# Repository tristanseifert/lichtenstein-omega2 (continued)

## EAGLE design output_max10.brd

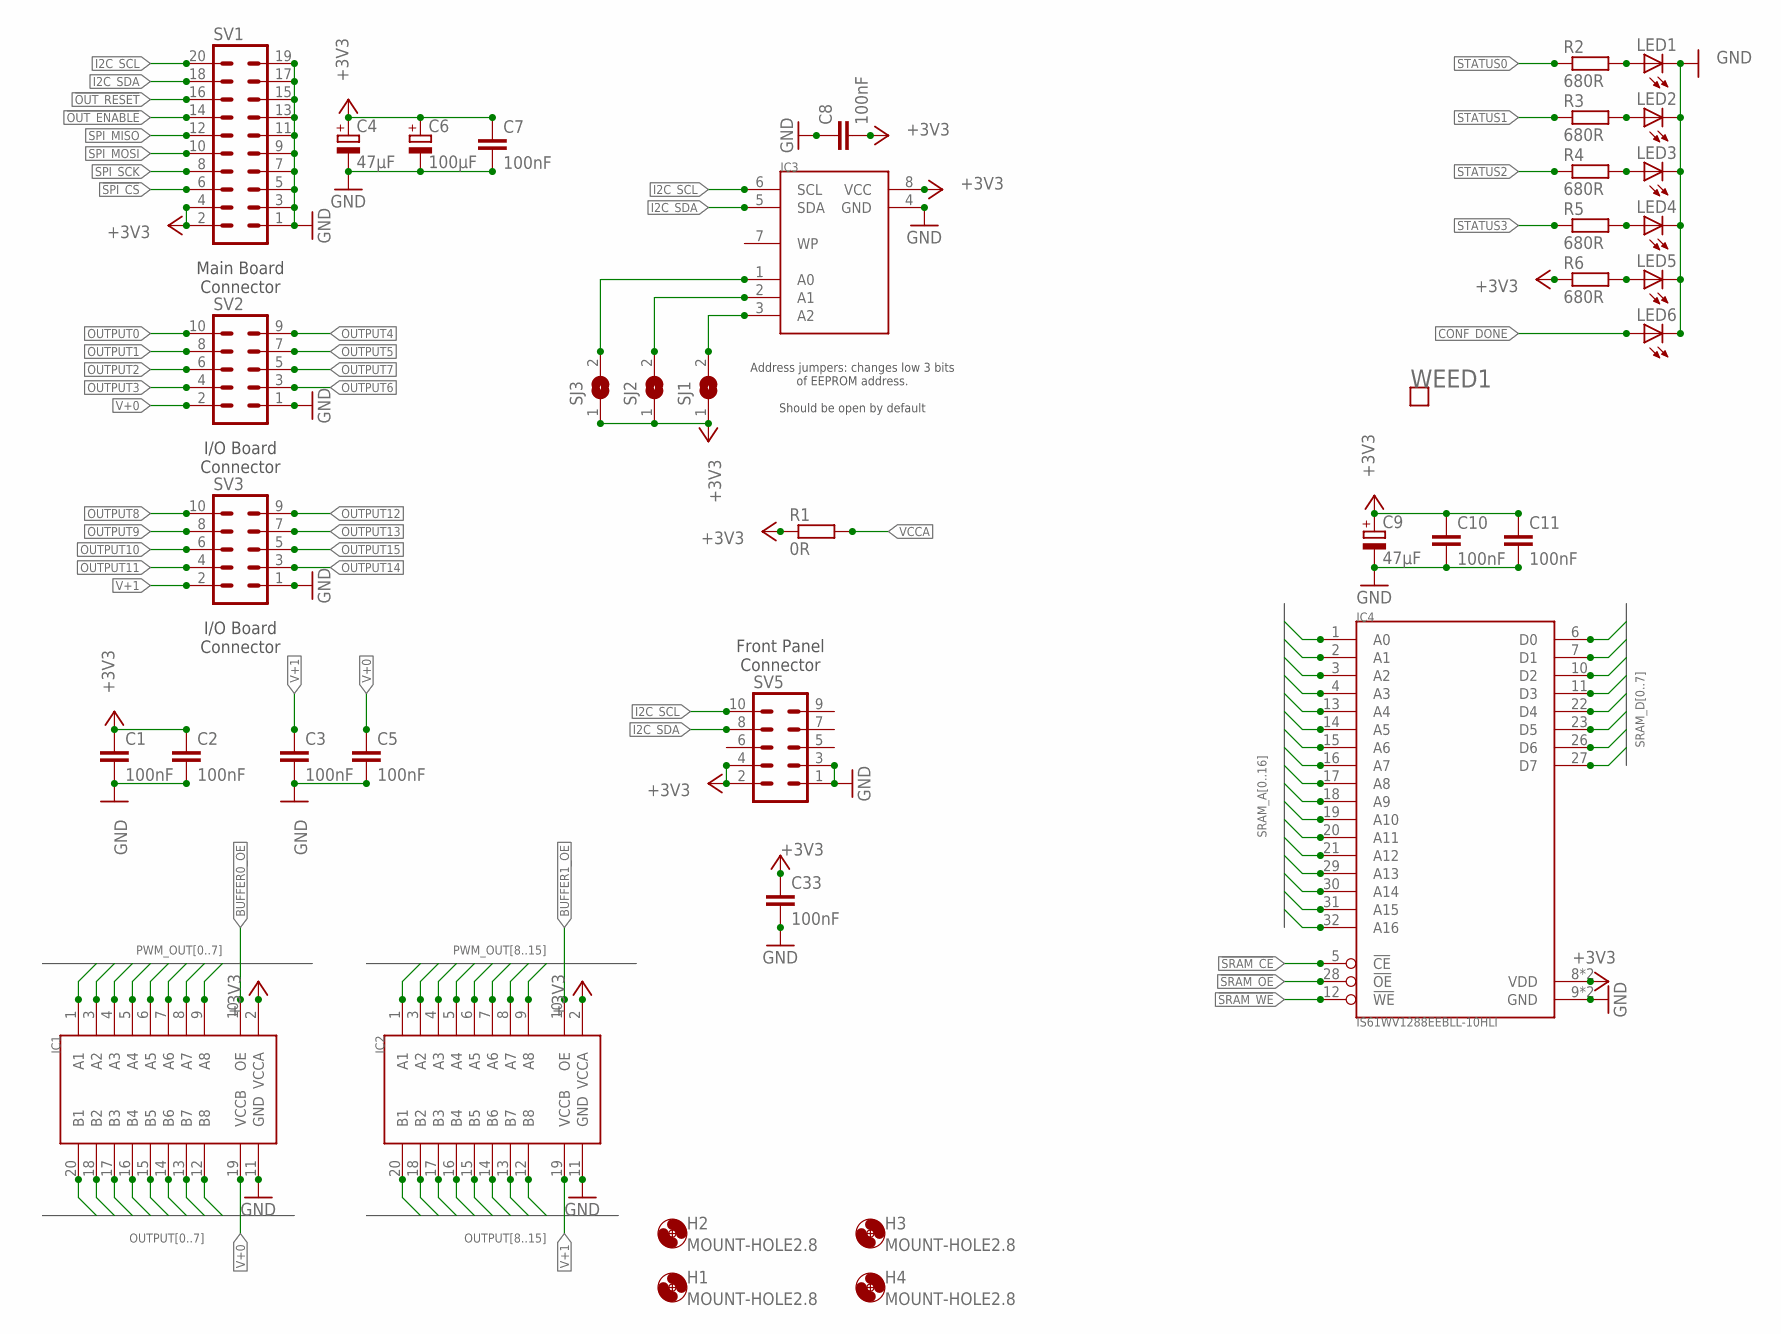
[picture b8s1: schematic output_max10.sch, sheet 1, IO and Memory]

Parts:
C1, C2, C3, C5, C7, C8, C10, C11, C33: 100nF; C0805; MOUSER 710-885012207072
C4, C9: 47µF; CT7343; MOUSER 581-TAJD476M016RNJV
C6: 100µF; CT7343; MOUSER 581-NOSD107M006
H1, H2, H3, H4: MOUNT-HOLE2.8; 2,8
IC1, IC2: TXB0108TSSOP20; TSSOP20
IC3: AT24C02DSOIC-8; SOIC8
IC4: IS61WV1288EEBLL-10HLI; TSOP8X16; MOUSER 870-61WV1288ELL10HLI
LED1: LEDCHIPLED_1206; CHIPLED_1206; MOUSER 604-APTR3216SRCPRV
LED2, LED3, LED4, LED5, LED6: LEDCHIPLED_1206; CHIPLED_1206; MOUSER 604-APTR3216SGC
R1: 0R; R2012; MOUSER 623-2508056017Y2
R2, R3, R4, R5, R6: 680R; M0805; MOUSER 652-CR0805-FX6800GLF
SJ1, SJ2, SJ3: SJ
SV1: MA10-2; MOUSER 517-30320-6002
SV2, SV3, SV5: MA05-2; MOUSER 517-30310-6002
WEED1: WEED; DOINK

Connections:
!OUT_ENABLE: SV1.14; also elsewhere on the board
!OUT_RESET: SV1.16; also elsewhere on the board
!SPI_CS: SV1.6; also elsewhere on the board
!SRAM_CE: IC4.5 (!CE); also elsewhere on the board
!SRAM_OE: IC4.28 (!OE); also elsewhere on the board
!SRAM_WE: IC4.12 (!WE); also elsewhere on the board
+3V3: C1.1, C2.1, C4.+, C6.+, C7.1, C8.2, C9.+, C10.1, C11.1, C33.1, IC1.2 (VCCA), IC2.2 (VCCA), IC3.8 (VCC), IC4.8 (VDD), IC4.24 (VDD), R1.1, R6.1, SJ1.1, SJ2.1, SJ3.1, SV1.2, SV1.4, SV5.2, SV5.4; also elsewhere on the board
BUFFER0_OE: IC1.10 (OE); also elsewhere on the board
BUFFER1_OE: IC2.10 (OE); also elsewhere on the board
CONF_DONE: LED6.A; also elsewhere on the board
GND: C1.2, C2.2, C3.2, C4.-, C5.2, C6.-, C7.2, C8.1, C9.-, C10.2, C11.2, C33.2, IC1.11 (GND), IC2.11 (GND), IC3.4 (GND), IC4.9 (GND), IC4.25 (GND), LED1.C, LED2.C, LED3.C, LED4.C, LED5.C, LED6.C, SV1.1, SV1.3, SV1.5, SV1.7, SV1.9, SV1.11, SV1.13, SV1.15, SV1.17, SV1.19, SV2.1, SV3.1, SV5.1, SV5.3; also elsewhere on the board
I2C_SCL: IC3.6 (SCL), SV1.20, SV5.10
I2C_SDA: IC3.5 (SDA), SV1.18, SV5.8
unnamed: LED3.A, R4.2
unnamed: LED4.A, R5.2
unnamed: LED5.A, R6.2
unnamed: IC3.3 (A2), SJ1.2
unnamed: IC3.2 (A1), SJ2.2
unnamed: IC3.1 (A0), SJ3.2
unnamed: LED1.A, R2.2
unnamed: LED2.A, R3.2
OUTPUT0: IC1.20 (B1), SV2.10
OUTPUT1: IC1.18 (B2), SV2.8
OUTPUT2: IC1.17 (B3), SV2.6
OUTPUT3: IC1.16 (B4), SV2.4
OUTPUT4: IC1.15 (B5), SV2.9
OUTPUT5: IC1.14 (B6), SV2.7
OUTPUT6: IC1.13 (B7), SV2.3
OUTPUT7: IC1.12 (B8), SV2.5
OUTPUT8: IC2.20 (B1), SV3.10
OUTPUT9: IC2.18 (B2), SV3.8
OUTPUT10: IC2.17 (B3), SV3.6
OUTPUT11: IC2.16 (B4), SV3.4
OUTPUT12: IC2.15 (B5), SV3.9
OUTPUT13: IC2.14 (B6), SV3.7
OUTPUT14: IC2.13 (B7), SV3.3
OUTPUT15: IC2.12 (B8), SV3.5
PWM_OUT0: IC1.9 (A8); also elsewhere on the board
PWM_OUT1: IC1.8 (A7); also elsewhere on the board
PWM_OUT2: IC1.7 (A6); also elsewhere on the board
PWM_OUT3: IC1.6 (A5); also elsewhere on the board
PWM_OUT4: IC1.5 (A4); also elsewhere on the board
PWM_OUT5: IC1.4 (A3); also elsewhere on the board
PWM_OUT6: IC1.3 (A2); also elsewhere on the board
PWM_OUT7: IC1.1 (A1); also elsewhere on the board
PWM_OUT8: IC2.9 (A8); also elsewhere on the board
PWM_OUT9: IC2.8 (A7); also elsewhere on the board
PWM_OUT10: IC2.7 (A6); also elsewhere on the board
PWM_OUT11: IC2.6 (A5); also elsewhere on the board
PWM_OUT12: IC2.5 (A4); also elsewhere on the board
PWM_OUT13: IC2.4 (A3); also elsewhere on the board
PWM_OUT14: IC2.3 (A2); also elsewhere on the board
PWM_OUT15: IC2.1 (A1); also elsewhere on the board
SPI_MISO: SV1.12; also elsewhere on the board
SPI_MOSI: SV1.10; also elsewhere on the board
SPI_SCK: SV1.8; also elsewhere on the board
SRAM_A0: IC4.1 (A0); also elsewhere on the board
SRAM_A1: IC4.2 (A1); also elsewhere on the board
SRAM_A2: IC4.3 (A2); also elsewhere on the board
SRAM_A3: IC4.4 (A3); also elsewhere on the board
SRAM_A4: IC4.13 (A4); also elsewhere on the board
SRAM_A5: IC4.14 (A5); also elsewhere on the board
SRAM_A6: IC4.15 (A6); also elsewhere on the board
SRAM_A7: IC4.16 (A7); also elsewhere on the board
SRAM_A8: IC4.17 (A8); also elsewhere on the board
SRAM_A9: IC4.18 (A9); also elsewhere on the board
SRAM_A10: IC4.19 (A10); also elsewhere on the board
SRAM_A11: IC4.20 (A11); also elsewhere on the board
SRAM_A12: IC4.21 (A12); also elsewhere on the board
SRAM_A13: IC4.29 (A13); also elsewhere on the board
SRAM_A14: IC4.30 (A14); also elsewhere on the board
SRAM_A15: IC4.31 (A15); also elsewhere on the board
SRAM_A16: IC4.32 (A16); also elsewhere on the board
SRAM_D0: IC4.6 (D0); also elsewhere on the board
SRAM_D1: IC4.7 (D1); also elsewhere on the board
SRAM_D2: IC4.10 (D2); also elsewhere on the board
SRAM_D3: IC4.11 (D3); also elsewhere on the board
SRAM_D4: IC4.22 (D4); also elsewhere on the board
SRAM_D5: IC4.23 (D5); also elsewhere on the board
SRAM_D6: IC4.26 (D6); also elsewhere on the board
SRAM_D7: IC4.27 (D7); also elsewhere on the board
STATUS0: R2.1; also elsewhere on the board
STATUS1: R3.1; also elsewhere on the board
STATUS2: R4.1; also elsewhere on the board
STATUS3: R5.1; also elsewhere on the board
V+0: C5.1, IC1.19 (VCCB), SV2.2
V+1: C3.1, IC2.19 (VCCB), SV3.2
VCCA: R1.2; also elsewhere on the board

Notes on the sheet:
Main Board Connector
I/O Board Connector
Front Panel Connector
Address jumpers: changes low 3 bits of EEPROM address. Should be open by default

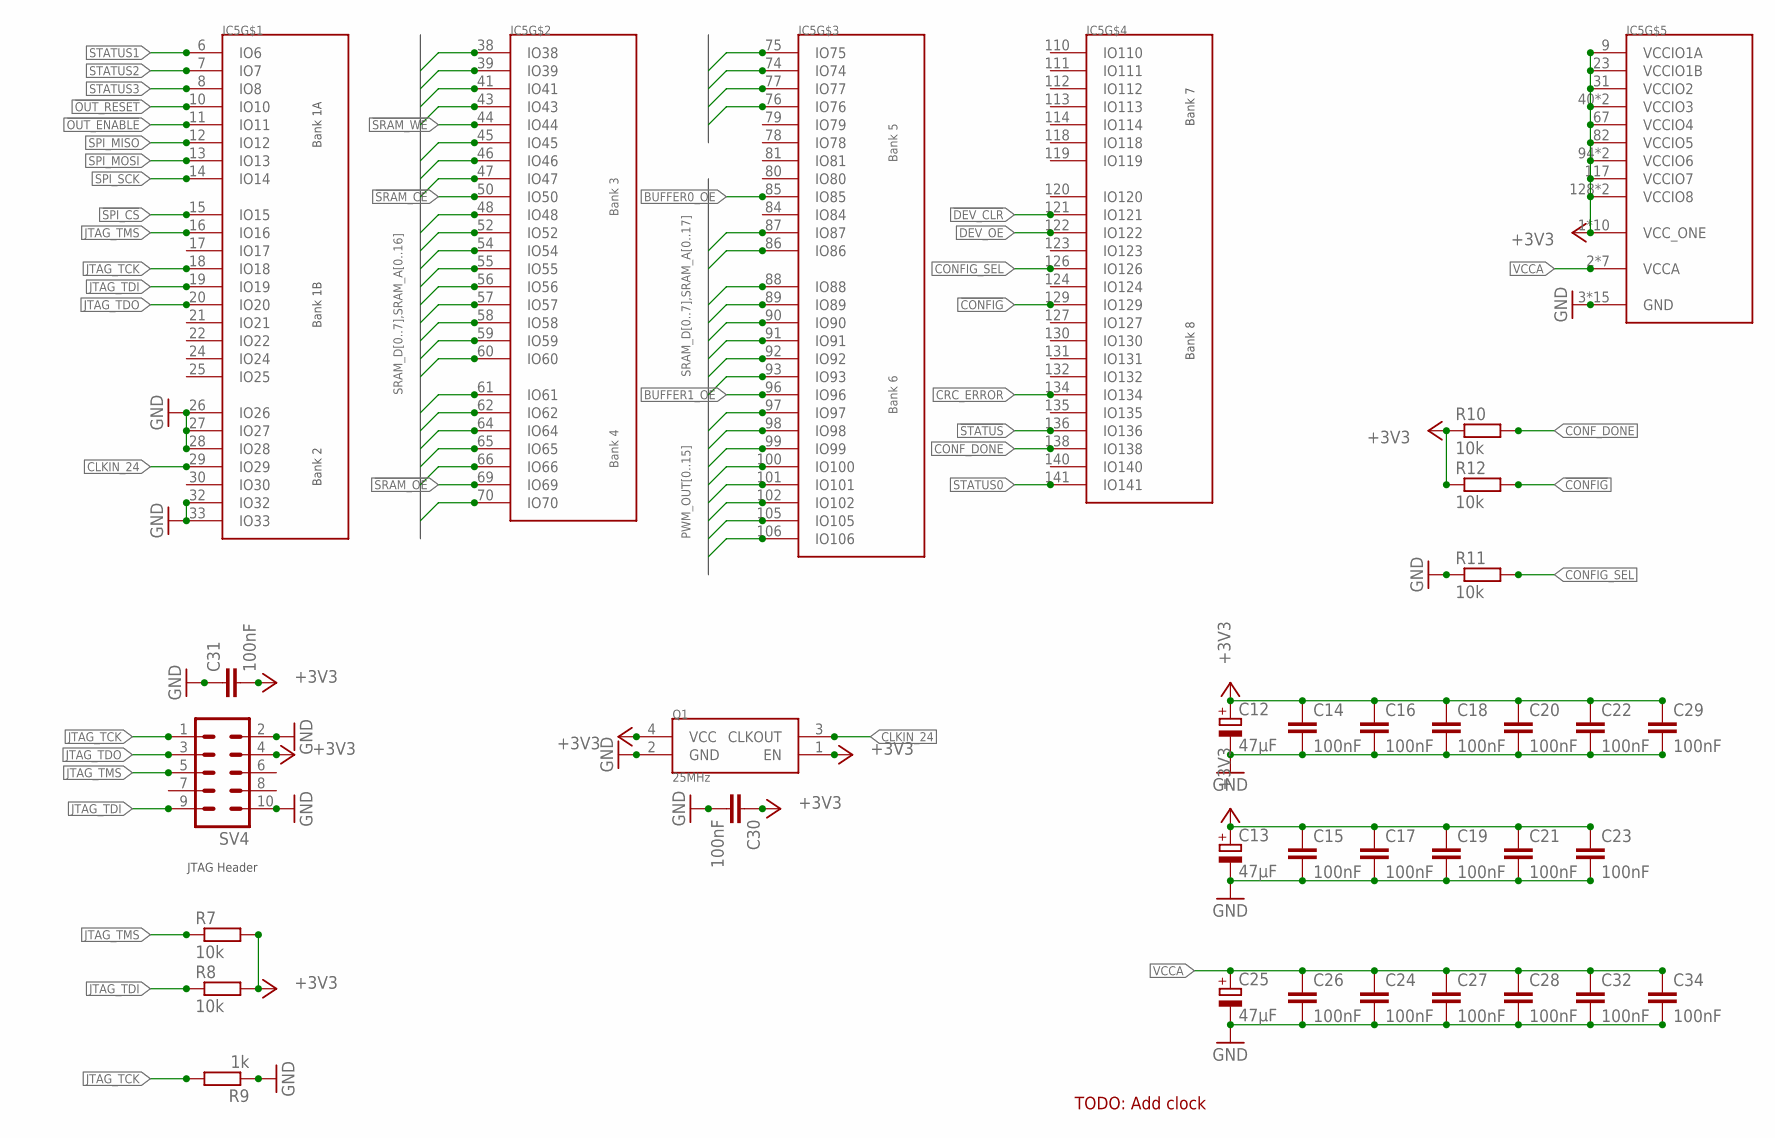
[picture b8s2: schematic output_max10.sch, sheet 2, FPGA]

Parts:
C12, C13, C25: 47µF; CT7343; MOUSER 581-TAJD476M016RNJV
C14, C15, C16, C17, C18, C19, C20, C21, C22, C23, C24, C26, C27, C28, C29, C30, C31, C32, C34: 100nF; C0805; MOUSER 710-885012207072
IC5: 10M04EQFP144; EQFP144; MOUSER 989-10M04SCE144C8G
Q1: 25MHz; VLGA-4; MOUSER 579-6101JI2A0240000T
R7, R8, R10, R11, R12: 10k; M0805; MOUSER 652-CR0805FX-1002ELF
R9: 1k; M0805; MOUSER 652-CR0805JW-102ELF
SV4: MA05-2; MOUSER 517-30310-6002

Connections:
!CONFIG: IC5.129 (IO129), R12.2
!DEV_CLR: IC5.121 (IO121)
!OUT_ENABLE: IC5.11 (IO11); also elsewhere on the board
!OUT_RESET: IC5.10 (IO10); also elsewhere on the board
!SPI_CS: IC5.15 (IO15); also elsewhere on the board
!SRAM_CE: IC5.50 (IO50); also elsewhere on the board
!SRAM_OE: IC5.69 (IO69); also elsewhere on the board
!SRAM_WE: IC5.44 (IO44); also elsewhere on the board
!STATUS: IC5.136 (IO136)
+3V3: C12.+, C13.+, C14.1, C15.1, C16.1, C17.1, C18.1, C19.1, C20.1, C21.1, C22.1, C23.1, C29.1, C30.1, C31.2, IC5.1 (VCC_ONE), IC5.9 (VCCIO1A), IC5.23 (VCCIO1B), IC5.31 (VCCIO2), IC5.36 (VCC_ONE), IC5.37 (VCC_ONE), IC5.40 (VCCIO3), IC5.49 (VCCIO3), IC5.51 (VCC_ONE), IC5.67 (VCCIO4), IC5.72 (VCC_ONE), IC5.73 (VCC_ONE), IC5.82 (VCCIO5), IC5.94 (VCCIO6), IC5.103 (VCCIO6), IC5.108 (VCC_ONE), IC5.109 (VCC_ONE), IC5.115 (VCC_ONE), IC5.117 (VCCIO7), IC5.128 (VCCIO8), IC5.139 (VCCIO8), IC5.144 (VCC_ONE), Q1.1 (EN), Q1.4 (VCC), R7.2, R8.2, R10.1, R12.1, SV4.4; also elsewhere on the board
BUFFER0_OE: IC5.85 (IO85); also elsewhere on the board
BUFFER1_OE: IC5.96 (IO96); also elsewhere on the board
CLKIN_24: IC5.29 (IO29), Q1.3 (CLKOUT)
CONFIG_SEL: IC5.126 (IO126), R11.2
CONF_DONE: IC5.138 (IO138), R10.2; also elsewhere on the board
CRC_ERROR: IC5.134 (IO134)
DEV_OE: IC5.122 (IO122)
GND: C12.-, C13.-, C14.2, C15.2, C16.2, C17.2, C18.2, C19.2, C20.2, C21.2, C22.2, C23.2, C24.2, C25.-, C26.2, C27.2, C28.2, C29.2, C30.2, C31.1, C32.2, C34.2, IC5.3 (GND), IC5.4 (GND), IC5.26 (IO26), IC5.27 (IO27), IC5.28 (IO28), IC5.32 (IO32), IC5.33 (IO33), IC5.42 (GND), IC5.53 (GND), IC5.63 (GND), IC5.68 (GND), IC5.83 (GND), IC5.95 (GND), IC5.104 (GND), IC5.116 (GND), IC5.125 (GND), IC5.133 (GND), IC5.137 (GND), IC5.142 (GND), IC5.PAD (GND), Q1.2 (GND), R9.1, R11.1, SV4.2, SV4.10; also elsewhere on the board
JTAG_TCK: IC5.18 (IO18), R9.2, SV4.1
JTAG_TDI: IC5.19 (IO19), R8.1, SV4.9
JTAG_TDO: IC5.20 (IO20), SV4.3
JTAG_TMS: IC5.16 (IO16), R7.1, SV4.5
PWM_OUT0: IC5.86 (IO86); also elsewhere on the board
PWM_OUT1: IC5.87 (IO87); also elsewhere on the board
PWM_OUT2: IC5.88 (IO88); also elsewhere on the board
PWM_OUT3: IC5.89 (IO89); also elsewhere on the board
PWM_OUT4: IC5.90 (IO90); also elsewhere on the board
PWM_OUT5: IC5.91 (IO91); also elsewhere on the board
PWM_OUT6: IC5.92 (IO92); also elsewhere on the board
PWM_OUT7: IC5.93 (IO93); also elsewhere on the board
PWM_OUT8: IC5.97 (IO97); also elsewhere on the board
PWM_OUT9: IC5.98 (IO98); also elsewhere on the board
PWM_OUT10: IC5.99 (IO99); also elsewhere on the board
PWM_OUT11: IC5.100 (IO100); also elsewhere on the board
PWM_OUT12: IC5.101 (IO101); also elsewhere on the board
PWM_OUT13: IC5.102 (IO102); also elsewhere on the board
PWM_OUT14: IC5.105 (IO105); also elsewhere on the board
PWM_OUT15: IC5.106 (IO106); also elsewhere on the board
SPI_MISO: IC5.12 (IO12); also elsewhere on the board
SPI_MOSI: IC5.13 (IO13); also elsewhere on the board
SPI_SCK: IC5.14 (IO14); also elsewhere on the board
SRAM_A0: IC5.56 (IO56); also elsewhere on the board
SRAM_A1: IC5.55 (IO55); also elsewhere on the board
SRAM_A2: IC5.54 (IO54); also elsewhere on the board
SRAM_A3: IC5.52 (IO52); also elsewhere on the board
SRAM_A4: IC5.43 (IO43); also elsewhere on the board
SRAM_A5: IC5.41 (IO41); also elsewhere on the board
SRAM_A6: IC5.39 (IO39); also elsewhere on the board
SRAM_A7: IC5.38 (IO38); also elsewhere on the board
SRAM_A8: IC5.57 (IO57); also elsewhere on the board
SRAM_A9: IC5.58 (IO58); also elsewhere on the board
SRAM_A10: IC5.59 (IO59); also elsewhere on the board
SRAM_A11: IC5.60 (IO60); also elsewhere on the board
SRAM_A12: IC5.61 (IO61); also elsewhere on the board
SRAM_A13: IC5.70 (IO70); also elsewhere on the board
SRAM_A14: IC5.76 (IO76); also elsewhere on the board
SRAM_A15: IC5.75 (IO75); also elsewhere on the board
SRAM_A16: IC5.74 (IO74); also elsewhere on the board
SRAM_A17: IC5.77 (IO77)
SRAM_D0: IC5.48 (IO48); also elsewhere on the board
SRAM_D1: IC5.47 (IO47); also elsewhere on the board
SRAM_D2: IC5.46 (IO46); also elsewhere on the board
SRAM_D3: IC5.45 (IO45); also elsewhere on the board
SRAM_D4: IC5.62 (IO62); also elsewhere on the board
SRAM_D5: IC5.64 (IO64); also elsewhere on the board
SRAM_D6: IC5.65 (IO65); also elsewhere on the board
SRAM_D7: IC5.66 (IO66); also elsewhere on the board
STATUS0: IC5.141 (IO141); also elsewhere on the board
STATUS1: IC5.6 (IO6); also elsewhere on the board
STATUS2: IC5.7 (IO7); also elsewhere on the board
STATUS3: IC5.8 (IO8); also elsewhere on the board
VCCA: C24.1, C25.+, C26.1, C27.1, C28.1, C32.1, C34.1, IC5.2 (VCCA), IC5.5 (VCCA), IC5.34 (VCCA), IC5.35 (VCCA), IC5.71 (VCCA), IC5.107 (VCCA), IC5.143 (VCCA); also elsewhere on the board

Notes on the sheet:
TODO: Add clock
JTAG Header

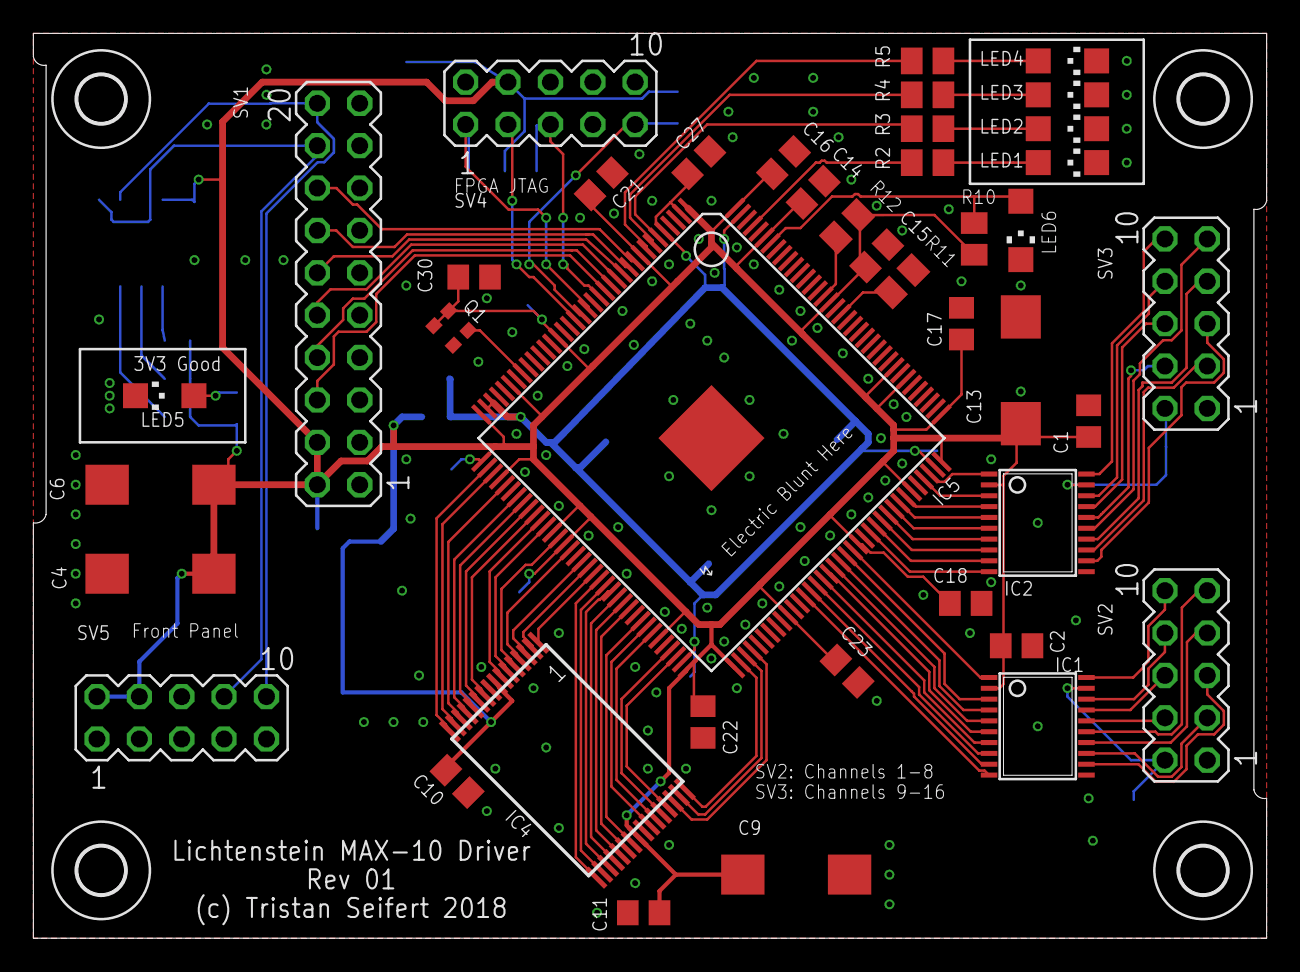
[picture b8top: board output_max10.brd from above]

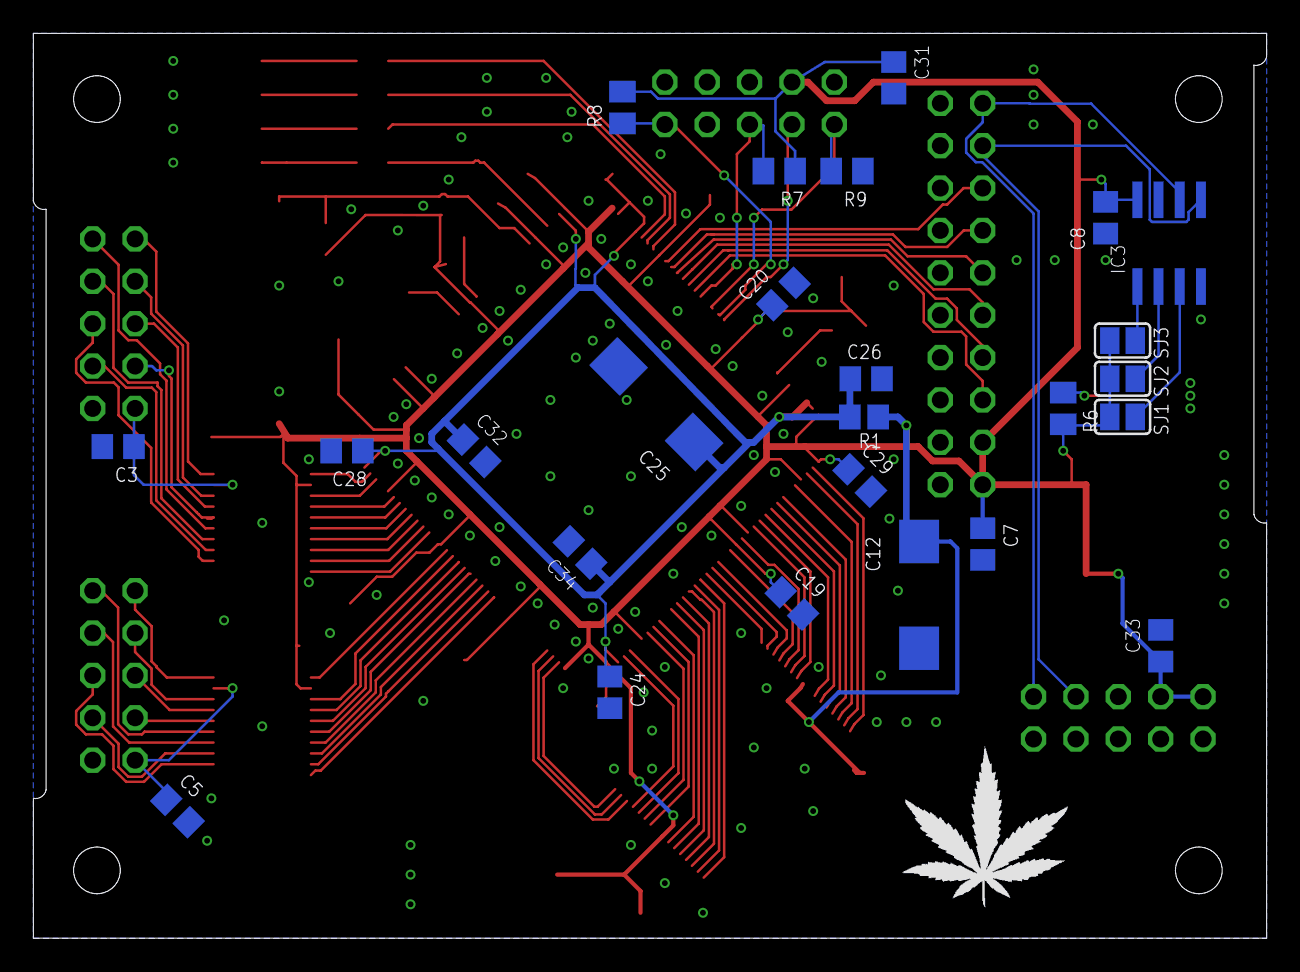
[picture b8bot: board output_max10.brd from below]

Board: 2 copper layers, 73.9 x 54.2 mm, 71 parts (26 on the bottom side), 95 nets.

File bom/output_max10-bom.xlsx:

Partlist exported from /Users/tristan/EAGLE/lichtenstein-omega2/output_max10.sc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
Part | Value | Device | Package | Description | MOUSER
C1 | 100nF | C-EUC0805 | C0805 | CAPACITOR, European symbol | 710-885012207072
C2 | 100nF | C-EUC0805 | C0805 | CAPACITOR, European symbol | 710-885012207072
C3 | 100nF | C-EUC0805 | C0805 | CAPACITOR, European symbol | 710-885012207072
C4 | 47µF | CPOL-EUCT7343 | CT7343 | POLARIZED CAPACITOR, European symbol | 581-TAJD476M016RNJV
C5 | 100nF | C-EUC0805 | C0805 | CAPACITOR, European symbol | 710-885012207072
C6 | 100µF | CPOL-EUCT7343 | CT7343 | POLARIZED CAPACITOR, European symbol | 581-NOSD107M006
C7 | 100nF | C-EUC0805 | C0805 | CAPACITOR, European symbol | 710-885012207072
C8 | 100nF | C-EUC0805 | C0805 | CAPACITOR, European symbol | 710-885012207072
C9 | 47µF | CPOL-EUCT7343 | CT7343 | POLARIZED CAPACITOR, European symbol | 581-TAJD476M016RNJV
C10 | 100nF | C-EUC0805 | C0805 | CAPACITOR, European symbol | 710-885012207072
C11 | 100nF | C-EUC0805 | C0805 | CAPACITOR, European symbol | 710-885012207072
C12 | 47µF | CPOL-EUCT7343 | CT7343 | POLARIZED CAPACITOR, European symbol | 581-TAJD476M016RNJV
C13 | 47µF | CPOL-EUCT7343 | CT7343 | POLARIZED CAPACITOR, European symbol | 581-TAJD476M016RNJV
C14 | 100nF | C-EUC0805 | C0805 | CAPACITOR, European symbol | 710-885012207072
C15 | 100nF | C-EUC0805 | C0805 | CAPACITOR, European symbol | 710-885012207072
C16 | 100nF | C-EUC0805 | C0805 | CAPACITOR, European symbol | 710-885012207072
C17 | 100nF | C-EUC0805 | C0805 | CAPACITOR, European symbol | 710-885012207072
C18 | 100nF | C-EUC0805 | C0805 | CAPACITOR, European symbol | 710-885012207072
C19 | 100nF | C-EUC0805 | C0805 | CAPACITOR, European symbol | 710-885012207072
C20 | 100nF | C-EUC0805 | C0805 | CAPACITOR, European symbol | 710-885012207072
C21 | 100nF | C-EUC0805 | C0805 | CAPACITOR, European symbol | 710-885012207072
C22 | 100nF | C-EUC0805 | C0805 | CAPACITOR, European symbol | 710-885012207072
C23 | 100nF | C-EUC0805 | C0805 | CAPACITOR, European symbol | 710-885012207072
C24 | 100nF | C-EUC0805 | C0805 | CAPACITOR, European symbol | 710-885012207072
C25 | 47µF | CPOL-EUCT7343 | CT7343 | POLARIZED CAPACITOR, European symbol | 581-TAJD476M016RNJV
C26 | 100nF | C-EUC0805 | C0805 | CAPACITOR, European symbol | 710-885012207072
C27 | 100nF | C-EUC0805 | C0805 | CAPACITOR, European symbol | 710-885012207072
C28 | 100nF | C-EUC0805 | C0805 | CAPACITOR, European symbol | 710-885012207072
C29 | 100nF | C-EUC0805 | C0805 | CAPACITOR, European symbol | 710-885012207072
C30 | 100nF | C-EUC0805 | C0805 | CAPACITOR, European symbol | 710-885012207072
C31 | 100nF | C-EUC0805 | C0805 | CAPACITOR, European symbol | 710-885012207072
C32 | 100nF | C-EUC0805 | C0805 | CAPACITOR, European symbol | 710-885012207072
C33 | 100nF | C-EUC0805 | C0805 | CAPACITOR, European symbol | 710-885012207072
C34 | 100nF | C-EUC0805 | C0805 | CAPACITOR, European symbol | 710-885012207072
IC1 |  | TXB0108TSSOP20 | TSSOP20 | 8-Bit Bidirectional Voltage-Level Translator with Auto-Direction Sensing and | 595-TXB0108PWR
IC2 |  | TXB0108TSSOP20 | TSSOP20 | 8-Bit Bidirectional Voltage-Level Translator with Auto-Direction Sensing and | 595-TXB0108PWR
IC3 |  | AT24C02DSOIC-8 | SOIC8 | I2C-Compatible (2-wire) Serial EEPROM; 1-Kbit (128 x 8) or 2-Kbit (256 x 8) | 556-AT24C02D-SSHM-T
IC4 | IS61WV1288EEBLL-10HLI | IS61WV1288EEBLLTSOP32-I | TSOP8X16 | 128K x 8 HIGH SPEED ASYNCHRONOUS CMOS STATIC RAM WITH ECC | 870-61WV1288ELL10HLI
IC5 | 10M04EQFP144 | 10M04EQFP144 | EQFP144 | 10M04SCE144 edit this description | 989-10M04SCE144C8G
LED1 |  | LEDCHIPLED_1206 | CHIPLED_1206 | LED | 604-APTR3216SRCPRV
LED2 |  | LEDCHIPLED_1206 | CHIPLED_1206 | LED | 604-APTR3216SGC
LED3 |  | LEDCHIPLED_1206 | CHIPLED_1206 | LED | 604-APTR3216SGC
LED4 |  | LEDCHIPLED_1206 | CHIPLED_1206 | LED | 604-APTR3216SGC
LED5 |  | LEDCHIPLED_1206 | CHIPLED_1206 | LED | 604-APTR3216SGC
LED6 |  | LEDCHIPLED_1206 | CHIPLED_1206 | LED | 604-APTR3216SGC
Q1 | 25MHz | DSC61XX | VLGA-4 | Ultra-Small, Ultra-Low Power MEMS Oscillator | 579-6101JI2A0240000T
R1 | 0R | R-EU_R2012 | R2012 | RESISTOR, European symbol | 623-2508056017Y2
R2 | 680R | R-EU_M0805 | M0805 | RESISTOR, European symbol | 652-CR0805-FX6800GLF
R3 | 680R | R-EU_M0805 | M0805 | RESISTOR, European symbol | 652-CR0805-FX6800GLF
R4 | 680R | R-EU_M0805 | M0805 | RESISTOR, European symbol | 652-CR0805-FX6800GLF
R5 | 680R | R-EU_M0805 | M0805 | RESISTOR, European symbol | 652-CR0805-FX6800GLF
R6 | 680R | R-EU_M0805 | M0805 | RESISTOR, European symbol | 652-CR0805-FX6800GLF
R7 | 10k | R-EU_M0805 | M0805 | RESISTOR, European symbol | 652-CR0805FX-1002ELF
R8 | 10k | R-EU_M0805 | M0805 | RESISTOR, European symbol | 652-CR0805FX-1002ELF
R9 | 1k | R-EU_M0805 | M0805 | RESISTOR, European symbol | 652-CR0805JW-102ELF
R10 | 10k/680R?? | R-EU_M0805 | M0805 | RESISTOR, European symbol | 652-CR0805FX-1002ELF
R11 | 10k | R-EU_M0805 | M0805 | RESISTOR, European symbol | 652-CR0805FX-1002ELF
R12 | 10k | R-EU_M0805 | M0805 | RESISTOR, European symbol | 652-CR0805FX-1002ELF
SV1 |  | MA10-2 | MA10-2 | PIN HEADER | 517-30320-6002
SV2 |  | MA05-2 | MA05-2 | PIN HEADER | 517-30310-6002
SV3 |  | MA05-2 | MA05-2 | PIN HEADER | 517-30310-6002
SV4 |  | MA05-2 | MA05-2 | PIN HEADER | 517-30310-6002
SV5 |  | MA05-2 | MA05-2 | PIN HEADER | 517-30310-6002

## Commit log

2018-05-01 Initial commit with Omega2 footprint and Ethernet
2018-05-01 add readme
2018-05-01 Added 3V3 and 1V8 voltage regulators
2018-05-02 Added CPLD, output drivers, IO expanders
2018-05-02 moved output CPLD to its own schematic/board
2018-05-02 Added mouser part numbers for most components
2018-05-02 began pcb layout for main board
2018-05-02 finished main board layout
2018-05-02 Rev01 sent to manufacture
2018-05-03 Finished 10M04 library part
2018-05-08 Added MAX10-based FPGA output waveform generator
2018-05-08 Added clock generator to FPGA (lol)
2018-05-09 minor revisions to layout on fpga board
2018-05-09 BOM for base board
2018-05-12 Added basic output board
2018-05-18 Fixed a few footprint issues and added explcit pull-ups for test inputs
2018-05-24 added license
2018-05-26 Fixed some more footprints on MAX10 driver
2018-05-27 clean up board some more; change eeprom to SOIC
2018-05-30 Fixed bulk capacitor footprints; made +V for output channels independent on output board
2018-05-31 Cleaned up output board; added pull-ups to inputs on Lichtenstein board; moved some decoupling caps on FPGA output board
2018-06-03 Added some required reisstors to FPGA outputboard
2018-06-03 rev 01 of fpga output board
2018-06-03 add max10 bom
2018-06-09 Tweaked footprints for wire terminals; fixed up some mechanical issues on output board (incl. removing resistor networks)
2018-06-09 Moved resistor network inputs slightly
2018-06-10 Added DE10 GPIO expander
2018-06-12 corrected output board bom
2018-06-12 Minor revisions to output board
2018-06-12 Got rid of resistor networks on lichtenstein board
2018-06-16 Minor component placemnet changes for MAX10 output board to fix mechanical issues
2018-06-20 Fixed some broken outputs; pwm output board added
2018-06-21 Cleaned up traces slightly for PWM board
2018-06-21 Added BoM for lichtenstein_pwm
2018-10-21 added 8ch spi mux schematic
2018-10-22 added mostly complete board for mux
2018-10-22 finished routing differential transceivers
2018-10-22 routed missing differential driver enables
2018-10-23 Added MCP2517FD CAN transceiver
2018-10-23 began work on differential output board
2018-10-24 fixed CAN termination for cat6 wiring
2018-10-24 added status LEDs for power on differential output board
2018-10-24 routed differential output board
2018-10-24 updated gitignore, unpushed changes for PWM-lichtenstein board
2018-10-24 Added footprint for STM32F042Fx chips
2018-10-25 added holes to differential output board
2018-10-25 Added STM32 as CAN bus controller to rpi board
2018-10-25 Added cortex debug header
2018-10-26 Cleaned up power for CAN controller
2018-10-27 Added I2C testpoints
2018-10-30 Added clock calibration signal to cannabus controller (divide 50MHz clk by 1000 in CPLD)
2018-10-30 More tweaks to the differential output board
2018-10-30 Cleaned up output and differential driver boards; added basic differential receiver board
2018-10-31 Finished output stage of differential LED board; started routing CANnabus controller/power sections
2018-10-31 Added LT6100 to measure current (todo: add shunt connections)
2018-11-01 finished routing LED board; substituted a few components and fixed missing level translation
2018-11-01 More updates to libraries
2018-11-03 moved status LEDs from debug pins to SPI pins
2018-11-04 added footprints for termination resistors on output connection board
2018-11-05 submitted rev 1 of output and led boards to board house
2018-11-13 rev01 of output_8ch_spi_mux sent to manufacturing
2018-12-07 rev2 of differential output board (fix capacitor footprint)
2018-12-09 more fixes to differential output board
2018-12-16 version 2 of pwm board for physical mounting
2018-12-16 power for pwm board
2018-12-17 routed most of the pwm board, need to finish with input connectors
2018-12-18 finished routing PWMv2 board
2018-12-20 added current sense amplifier; replaced footprints of some large resevoir caps
2018-12-21 removed input connector, cleaned up some signals
2018-12-21 more aesthetic fixes to board
2018-12-22 more board clean-up
2018-12-22 moved i2c expander more underneath omega module
2018-12-23 pwm board v2: rev 01 sent to pcb fab
2019-09-29 add controller meeper
